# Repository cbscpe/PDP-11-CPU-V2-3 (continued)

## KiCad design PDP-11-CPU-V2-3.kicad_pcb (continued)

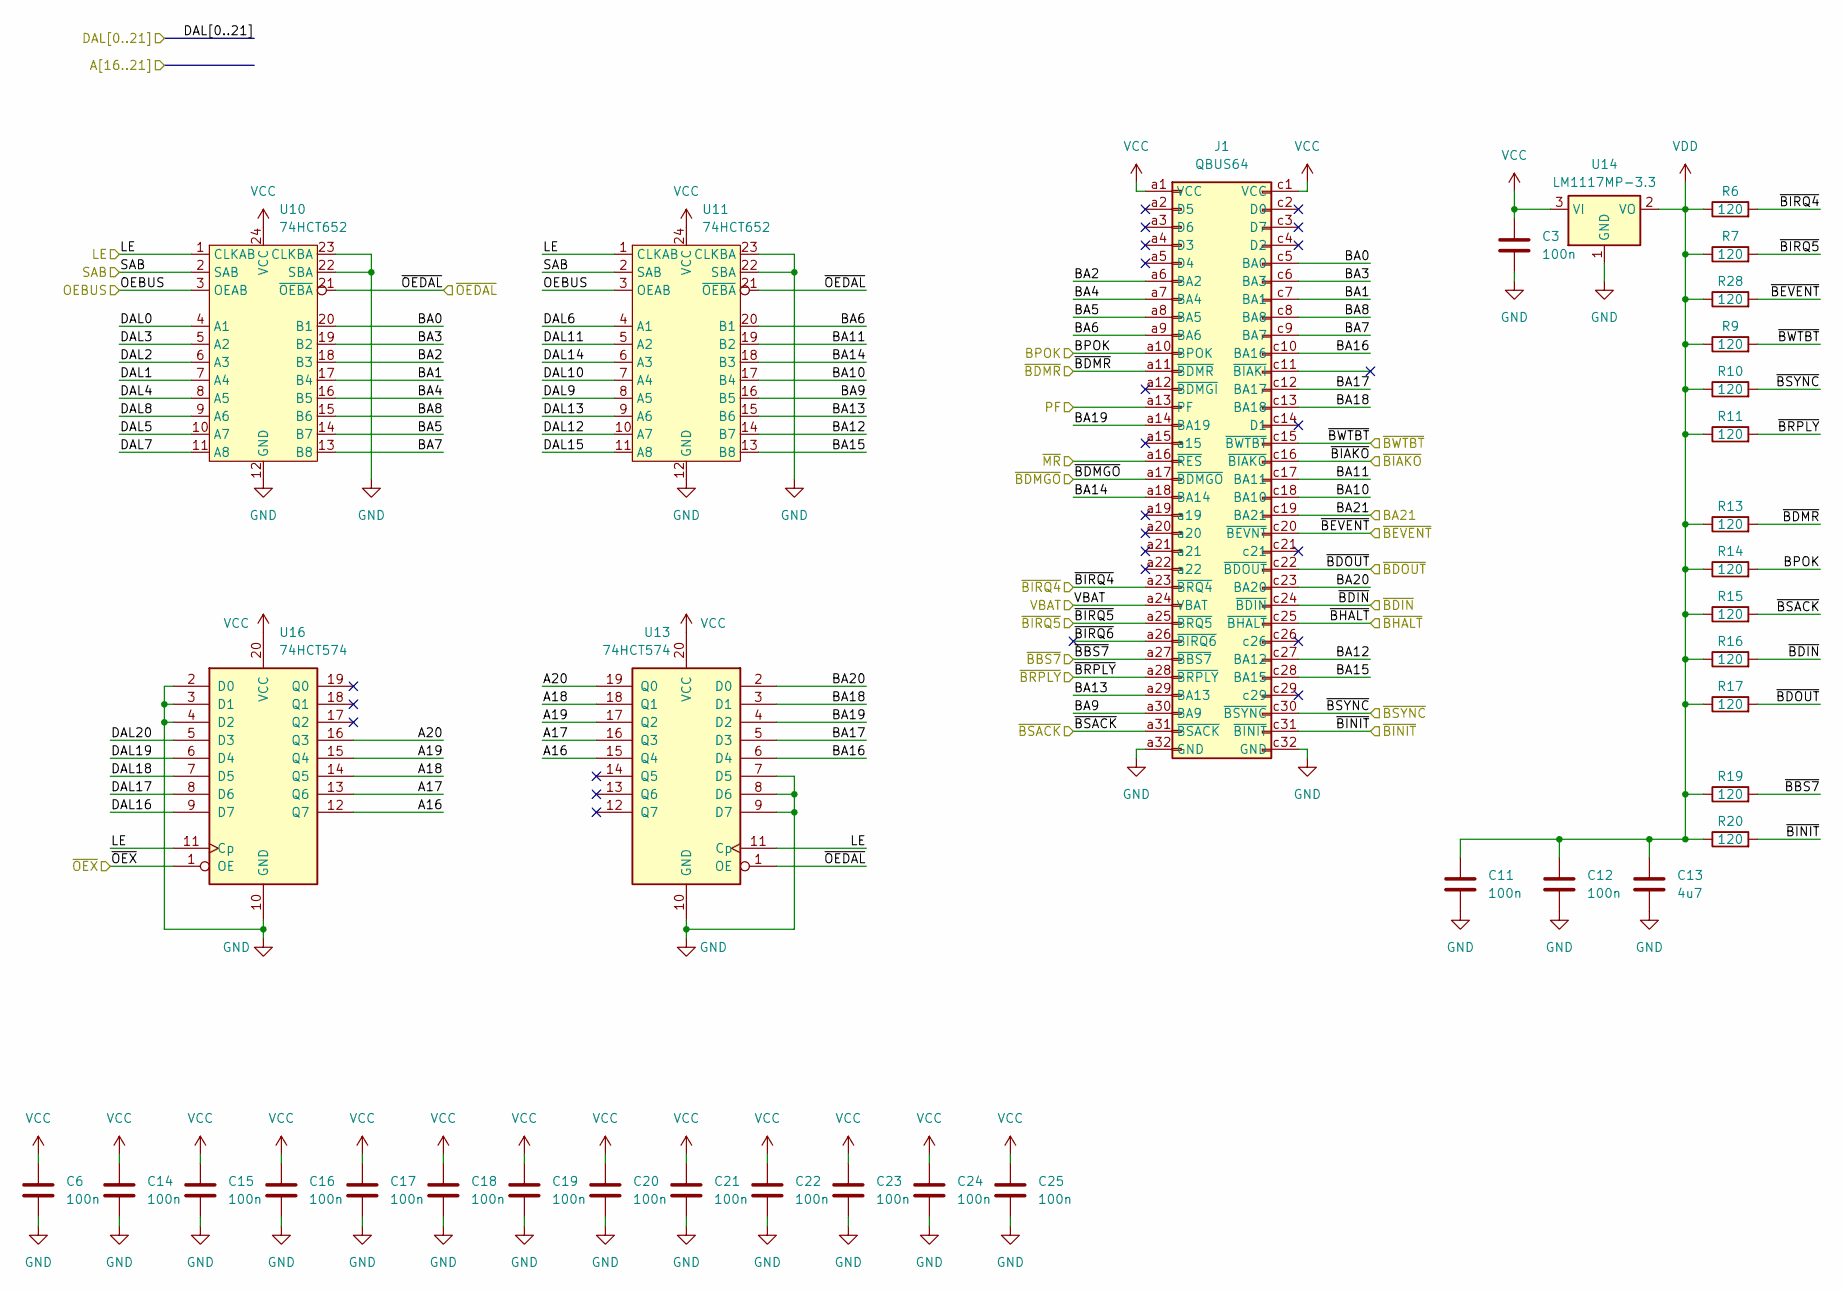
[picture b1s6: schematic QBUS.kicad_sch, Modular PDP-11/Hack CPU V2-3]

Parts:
C3, C6, C11, C12, C14, C15, C16, C17, C18, C19, C20, C21, C22, C23, C24, C25: 100n; C_0603_1608Metric_Pad1.08x0.95mm_HandSolder
C13: 4u7; CP_EIA-3528-12_Kemet-T_HandSolder
J1: QBUS64; DIN41612_C_2x32_Male_Horizontal_THT
R6, R7, R9, R10, R11, R13, R14, R15, R16, R17, R19, R20, R28: 120; R_0603_1608Metric_Pad0.98x0.95mm_HandSolder
U10, U11: 74HCT652; SOIC-24W_7.5x15.4mm_P1.27mm
U13, U16: 74HCT574; TSSOP-20_4.4x6.5mm_P0.65mm
U14: LM1117MP-3.3; SOT-223-3_TabPin2

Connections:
/A16: U13.15 (Q4), U16.12 (Q7); also elsewhere on the board
/A17: U13.16 (Q3), U16.13 (Q6); also elsewhere on the board
/A18: U13.18 (Q1), U16.14 (Q5); also elsewhere on the board
/A19: U13.17 (Q2), U16.15 (Q4); also elsewhere on the board
/A20: U13.19 (Q0), U16.16 (Q3); also elsewhere on the board
/BA21: J1.c19 (BA21); also elsewhere on the board
/BPOK: J1.a10 (BPOK), R14.2; also elsewhere on the board
/DAL0: U10.4 (A1); also elsewhere on the board
/DAL1: U10.7 (A4); also elsewhere on the board
/DAL2: U10.6 (A3); also elsewhere on the board
/DAL3: U10.5 (A2); also elsewhere on the board
/DAL4: U10.8 (A5); also elsewhere on the board
/DAL5: U10.10 (A7); also elsewhere on the board
/DAL6: U11.4 (A1); also elsewhere on the board
/DAL7: U10.11 (A8); also elsewhere on the board
/DAL8: U10.9 (A6); also elsewhere on the board
/DAL9: U11.8 (A5); also elsewhere on the board
/DAL10: U11.7 (A4); also elsewhere on the board
/DAL11: U11.5 (A2); also elsewhere on the board
/DAL12: U11.10 (A7); also elsewhere on the board
/DAL13: U11.9 (A6); also elsewhere on the board
/DAL14: U11.6 (A3); also elsewhere on the board
/DAL15: U11.11 (A8); also elsewhere on the board
/DAL16: U16.9 (D7); also elsewhere on the board
/DAL17: U16.8 (D6); also elsewhere on the board
/DAL18: U16.7 (D5); also elsewhere on the board
/DAL19: U16.6 (D4); also elsewhere on the board
/DAL20: U16.5 (D3); also elsewhere on the board
/LE: U10.1 (CLKAB), U11.1 (CLKAB), U13.11 (Cp), U16.11 (Cp); also elsewhere on the board
/OEBUS: U10.3 (OEAB), U11.3 (OEAB); also elsewhere on the board
/PF: J1.a13 (PF); also elsewhere on the board
/QBUS/BA0: J1.c5 (BA0), U10.20 (B1)
/QBUS/BA1: J1.c7 (BA1), U10.17 (B4)
/QBUS/BA2: J1.a6 (BA2), U10.18 (B3)
/QBUS/BA3: J1.c6 (BA3), U10.19 (B2)
/QBUS/BA4: J1.a7 (BA4), U10.16 (B5)
/QBUS/BA5: J1.a8 (BA5), U10.14 (B7)
/QBUS/BA6: J1.a9 (BA6), U11.20 (B1)
/QBUS/BA7: J1.c9 (BA7), U10.13 (B8)
/QBUS/BA8: J1.c8 (BA8), U10.15 (B6)
/QBUS/BA9: J1.a30 (BA9), U11.16 (B5)
/QBUS/BA10: J1.c18 (BA10), U11.17 (B4)
/QBUS/BA11: J1.c17 (BA11), U11.19 (B2)
/QBUS/BA12: J1.c27 (BA12), U11.14 (B7)
/QBUS/BA13: J1.a29 (BA13), U11.15 (B6)
/QBUS/BA14: J1.a18 (BA14), U11.18 (B3)
/QBUS/BA15: J1.c28 (BA15), U11.13 (B8)
/QBUS/BA16: J1.c10 (BA16), U13.6 (D4)
/QBUS/BA17: J1.c12 (BA17), U13.5 (D3)
/QBUS/BA18: J1.c13 (BA18), U13.3 (D1)
/QBUS/BA19: J1.a14 (BA19), U13.4 (D2)
/QBUS/BA20: J1.c23 (BA20), U13.2 (D0)
/QBUS/~BIRQ6: J1.a26 (~BIRQ6)
/SAB: U10.2 (SAB), U11.2 (SAB); also elsewhere on the board
/VBAT: J1.a24 (VBAT); also elsewhere on the board
/~BBS7: J1.a27 (~BBS7), R19.2; also elsewhere on the board
/~BDIN: J1.c24 (~BDIN), R16.2; also elsewhere on the board
/~BDMGO: J1.a17 (~BDMGO); also elsewhere on the board
/~BDMR: J1.a11 (~BDMR), R13.2; also elsewhere on the board
/~BDOUT: J1.c22 (~BDOUT), R17.2; also elsewhere on the board
/~BEVENT: J1.c20 (~BEVNT), R28.2; also elsewhere on the board
/~BHALT: J1.c25 (~BHALT)
/~BIAKO: J1.c16 (~BIAKO); also elsewhere on the board
/~BINIT: J1.c31 (~BINIT), R20.2; also elsewhere on the board
/~BIRQ4: J1.a23 (~BRQ4), R6.2; also elsewhere on the board
/~BIRQ5: J1.a25 (~BRQ5), R7.2; also elsewhere on the board
/~BRPLY: J1.a28 (~BRPLY), R11.2; also elsewhere on the board
/~BSACK: J1.a31 (~BSACK), R15.2; also elsewhere on the board
/~BSYNC: J1.c30 (~BSYNC), R10.2; also elsewhere on the board
/~BWTBT: J1.c15 (~BWTBT), R9.2; also elsewhere on the board
/~MR: J1.a16 (~RES); also elsewhere on the board
/~OEDAL: U10.21 (~OEBA), U11.21 (~OEBA), U13.1 (OE); also elsewhere on the board
/~OEX: U16.1 (OE); also elsewhere on the board
GND: C3.2, C6.2, C11.2, C12.2, C13.2, C14.2, C15.2, C16.2, C17.2, C18.2, C19.2, C20.2, C21.2, C22.2, C23.2, C24.2, C25.2, J1.a32 (GND), J1.c32 (GND), U10.12 (GND), U10.22 (SBA), U10.23 (CLKBA), U11.12 (GND), U11.22 (SBA), U11.23 (CLKBA), U13.7 (D5), U13.8 (D6), U13.9 (D7), U13.10 (GND), U14.1 (GND), U16.2 (D0), U16.3 (D1), U16.4 (D2), U16.10 (GND); also elsewhere on the board
VCC: C3.1, C6.1, C14.1, C15.1, C16.1, C17.1, C18.1, C19.1, C20.1, C21.1, C22.1, C23.1, C24.1, C25.1, J1.a1 (VCC), J1.c1 (VCC), U10.24 (VCC), U11.24 (VCC), U13.20 (VCC), U14.3 (VI), U16.20 (VCC); also elsewhere on the board
VDD: C11.1, C12.1, C13.1, R6.1, R7.1, R9.1, R10.1, R11.1, R13.1, R14.1, R15.1, R16.1, R17.1, R19.1, R20.1, R28.1, U14.2 (VO)

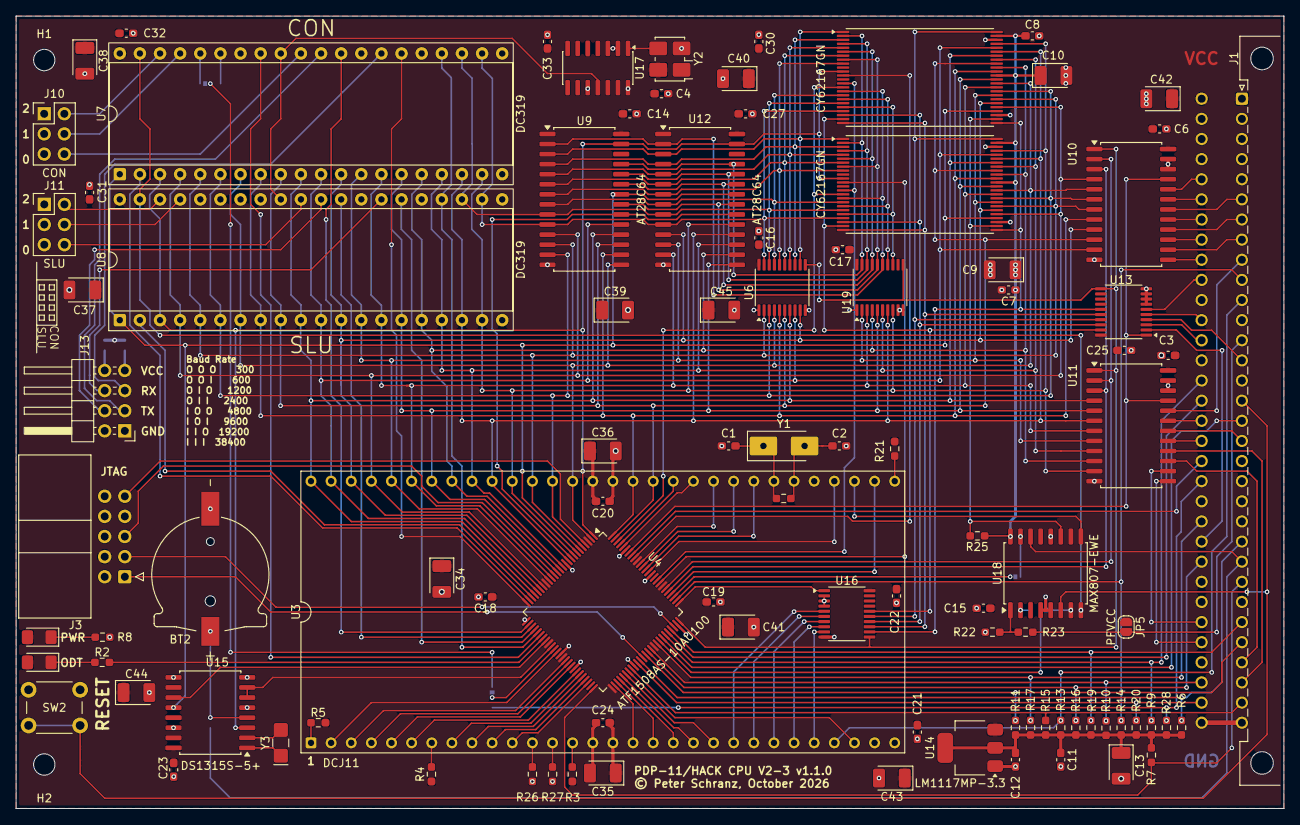
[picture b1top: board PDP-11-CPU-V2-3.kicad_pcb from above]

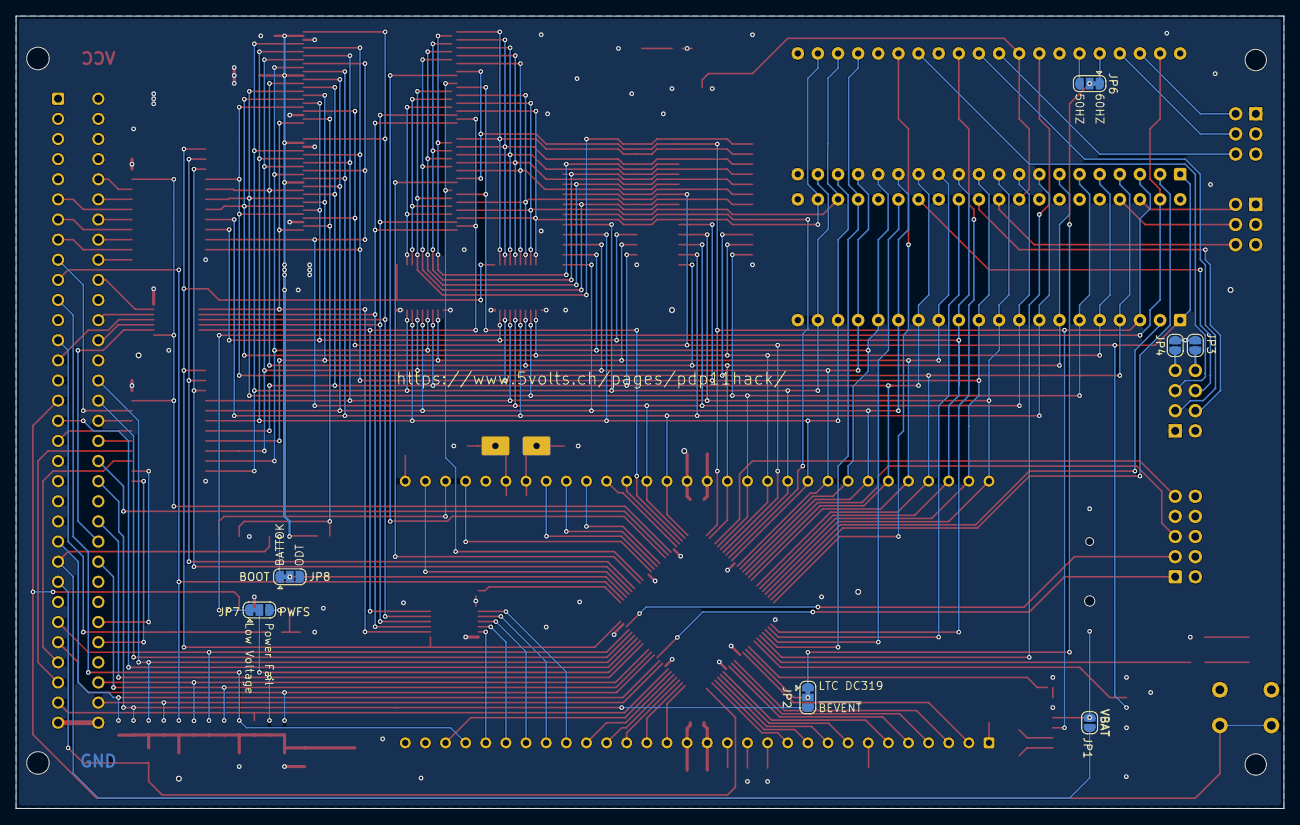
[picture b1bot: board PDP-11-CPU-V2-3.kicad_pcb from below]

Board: 2 copper layers, 160.0 x 100.0 mm, 106 parts (7 on the bottom side), 174 nets.

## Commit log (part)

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2026-06-27 New Page with CPU and Main CPLD
2026-06-28 Route PF and MR differently
2026-06-28 Connect BA21 to U13 and DAL21 to U16 and use the muxed output to connect as A21 to the ATF1508
2026-06-28 Reroute PF, MR
